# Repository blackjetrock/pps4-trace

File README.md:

# pps4-trace

Circuit to attempt to trace the address and data busses of the PPS-4 processor. the aim is to capture the ROM contents by sniffing the bus.
PPS-4 runs on -17V so circuit sits on 0V to -17v and divides down the inputs to 3V3.
PSU runs off PPS-4 supply

There's a few ROM image files I've managed to capture.

Although the bus tracing worked, it was difficult to work out exactly which ROM was bank switched and when. I therefore built a ROM dumper, desoldered a set of ROMs from a 920 and dumped them. This gave me the bank switching regime as the ROMs only responded to certain addressing. These ROMs were concatenated, effectively, and can be run in the simulator.
Details of the bank switching are in the simulator ROM file.

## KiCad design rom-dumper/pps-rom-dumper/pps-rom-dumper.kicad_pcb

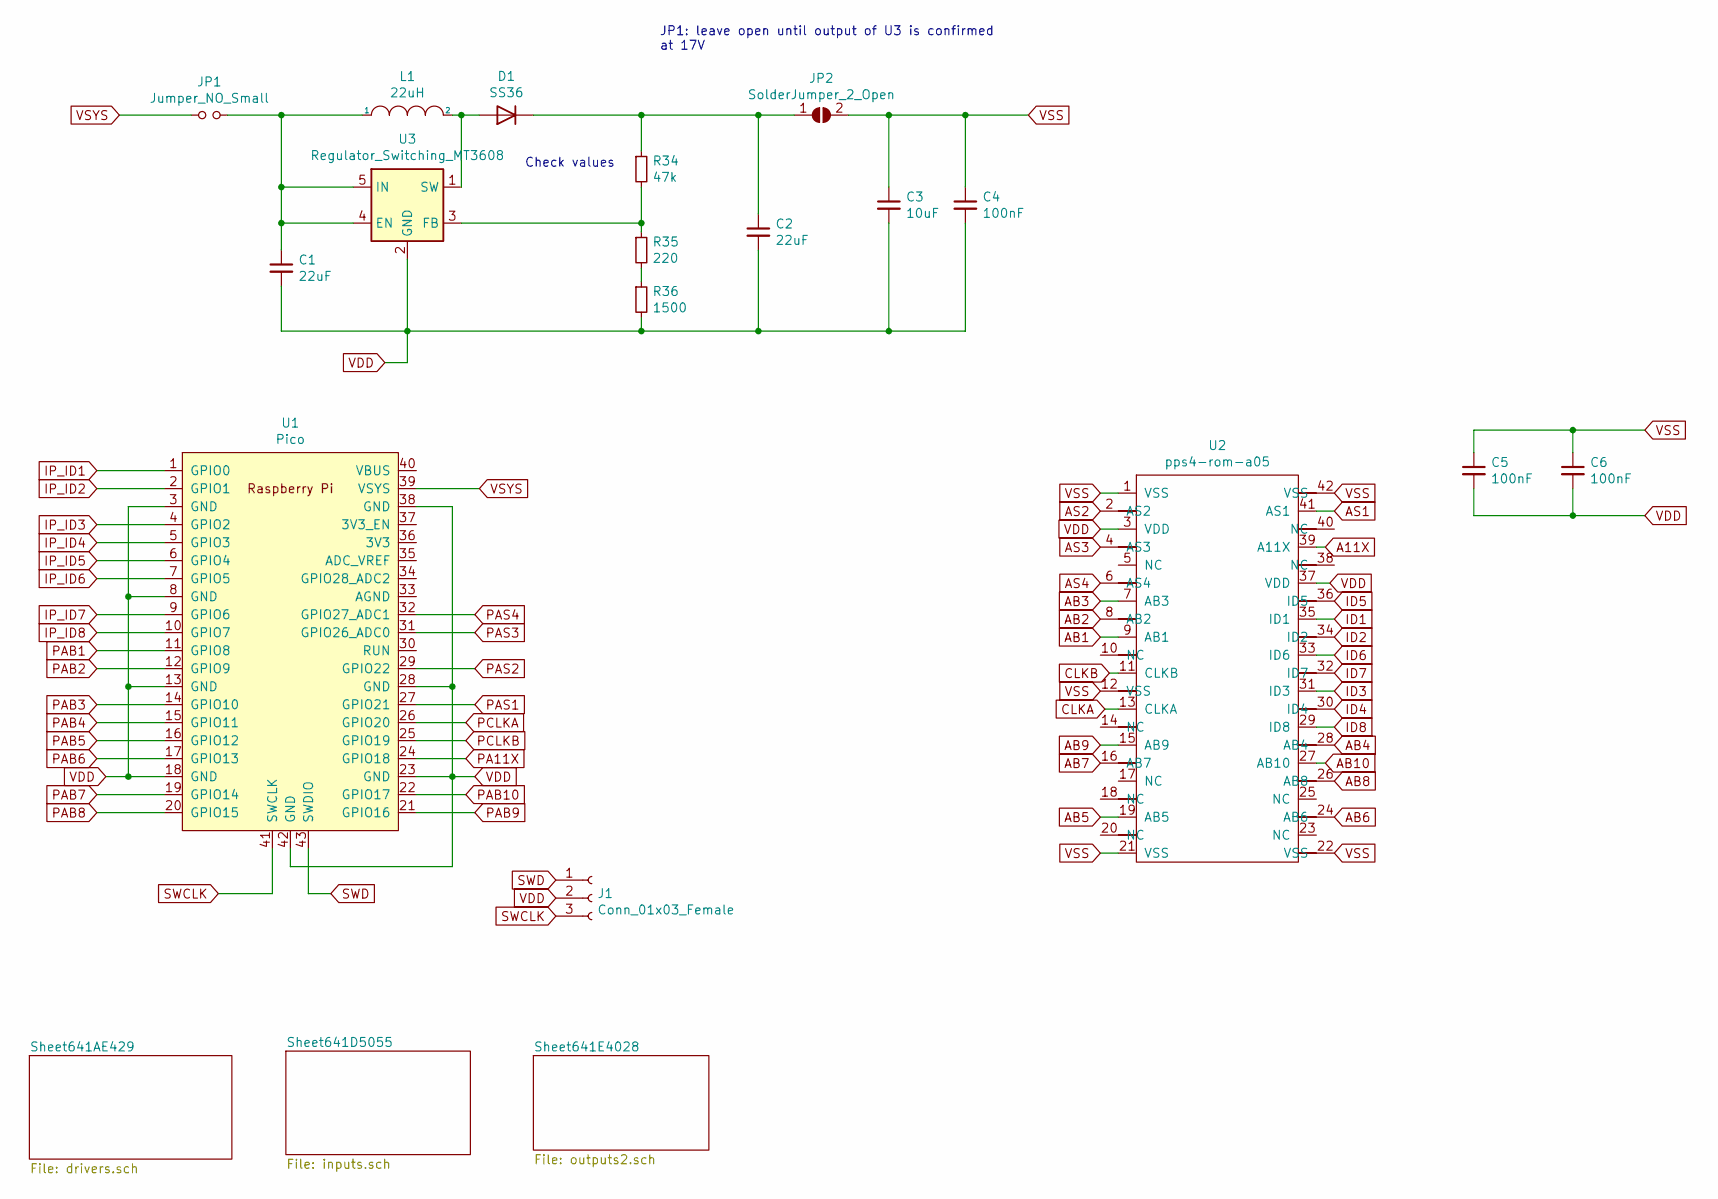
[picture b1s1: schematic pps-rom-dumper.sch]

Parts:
C1, C2: 22uF; C_1210_3225Metric_Pad1.33x2.70mm_HandSolder
C3: 10uF; C_1210_3225Metric_Pad1.33x2.70mm_HandSolder
C4, C5, C6: 100nF; C_1210_3225Metric_Pad1.33x2.70mm_HandSolder
D1: SS36; D_SOD-123
J1: Conn_01x03_Female; PinHeader_1x03_P2.54mm_Vertical
JP1: Jumper_NO_Small; SolderJumper-2_P1.3mm_Open_Pad0.8x0.8mm
JP2: SolderJumper_2_Open; SolderJumper-2_P1.3mm_Open_Pad0.8x0.8mm
L1: 22uH; L_Coilcraft_LPS5030
R34: 47k; R_0805_2012Metric
R35: 220; R_0805_2012Metric
R36: 1500; R_0805_2012Metric
U1: Pico; RPi_Pico_SMD_TH
U2: pps4-rom-a05; qip42
U3: Regulator_Switching_MT3608; SOT-23-6

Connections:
A11X: U2.39 (A11X); also elsewhere on the board
AB1: U2.9 (AB1); also elsewhere on the board
AB2: U2.8 (AB2); also elsewhere on the board
AB3: U2.7 (AB3); also elsewhere on the board
AB4: U2.28 (AB4); also elsewhere on the board
AB5: U2.19 (AB5); also elsewhere on the board
AB6: U2.24 (AB6); also elsewhere on the board
AB7: U2.16 (AB7); also elsewhere on the board
AB8: U2.26 (AB8); also elsewhere on the board
AB9: U2.15 (AB9); also elsewhere on the board
AB10: U2.27 (AB10); also elsewhere on the board
AS1: U2.41 (AS1); also elsewhere on the board
AS2: U2.2 (AS2); also elsewhere on the board
AS3: U2.4 (AS3); also elsewhere on the board
AS4: U2.6 (AS4); also elsewhere on the board
CLKA: U2.13 (CLKA); also elsewhere on the board
CLKB: U2.11 (CLKB); also elsewhere on the board
ID1: U2.35 (ID1); also elsewhere on the board
ID2: U2.34 (ID2); also elsewhere on the board
ID3: U2.31 (ID3); also elsewhere on the board
ID4: U2.30 (ID4); also elsewhere on the board
ID5: U2.36 (ID5); also elsewhere on the board
ID6: U2.33 (ID6); also elsewhere on the board
ID7: U2.32 (ID7); also elsewhere on the board
ID8: U2.29 (ID8); also elsewhere on the board
IP_ID1: U1.1 (GPIO0); also elsewhere on the board
IP_ID2: U1.2 (GPIO1); also elsewhere on the board
IP_ID3: U1.4 (GPIO2); also elsewhere on the board
IP_ID4: U1.5 (GPIO3); also elsewhere on the board
IP_ID5: U1.6 (GPIO4); also elsewhere on the board
IP_ID6: U1.7 (GPIO5); also elsewhere on the board
IP_ID7: U1.9 (GPIO6); also elsewhere on the board
IP_ID8: U1.10 (GPIO7); also elsewhere on the board
unnamed: C1.1, JP1.2, L1.1, U3.4 (EN), U3.5 (IN)
unnamed: C2.1, D1.1 (K), JP2.1 (A), R34.1
unnamed: D1.2 (A), L1.2, U3.1 (SW)
unnamed: R34.2, R35.1, U3.3 (FB)
unnamed: R35.2, R36.1
PA11X: U1.24 (GPIO18)
PAB1: U1.11 (GPIO8); also elsewhere on the board
PAB2: U1.12 (GPIO9); also elsewhere on the board
PAB3: U1.14 (GPIO10); also elsewhere on the board
PAB4: U1.15 (GPIO11); also elsewhere on the board
PAB5: U1.16 (GPIO12); also elsewhere on the board
PAB6: U1.17 (GPIO13); also elsewhere on the board
PAB7: U1.19 (GPIO14); also elsewhere on the board
PAB8: U1.20 (GPIO15); also elsewhere on the board
PAB9: U1.21 (GPIO16); also elsewhere on the board
PAB10: U1.22 (GPIO17); also elsewhere on the board
PAS1: U1.27 (GPIO21); also elsewhere on the board
PAS2: U1.29 (GPIO22); also elsewhere on the board
PAS3: U1.31 (GPIO26_ADC0); also elsewhere on the board
PAS4: U1.32 (GPIO27_ADC1); also elsewhere on the board
PCLKA: U1.26 (GPIO20); also elsewhere on the board
PCLKB: U1.25 (GPIO19); also elsewhere on the board
SWCLK: J1.3, U1.41 (SWCLK)
SWD: J1.1, U1.43 (SWDIO)
VDD: C1.2, C2.2, C3.2, C4.2, C5.2, C6.2, J1.2, R36.2, U1.3 (GND), U1.8 (GND), U1.13 (GND), U1.18 (GND), U1.23 (GND), U1.28 (GND), U1.38 (GND), U1.42 (GND), U2.3 (VDD), U2.37 (VDD), U3.2 (GND); also elsewhere on the board
VSS: C3.1, C4.1, C5.1, C6.1, JP2.2 (B), U2.1 (VSS), U2.12 (VSS), U2.21 (VSS), U2.22 (VSS), U2.42 (VSS); also elsewhere on the board
VSYS: JP1.1, U1.39 (VSYS)

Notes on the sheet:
Check values
JP1: leave open until output of U3 is confirmed at 17V

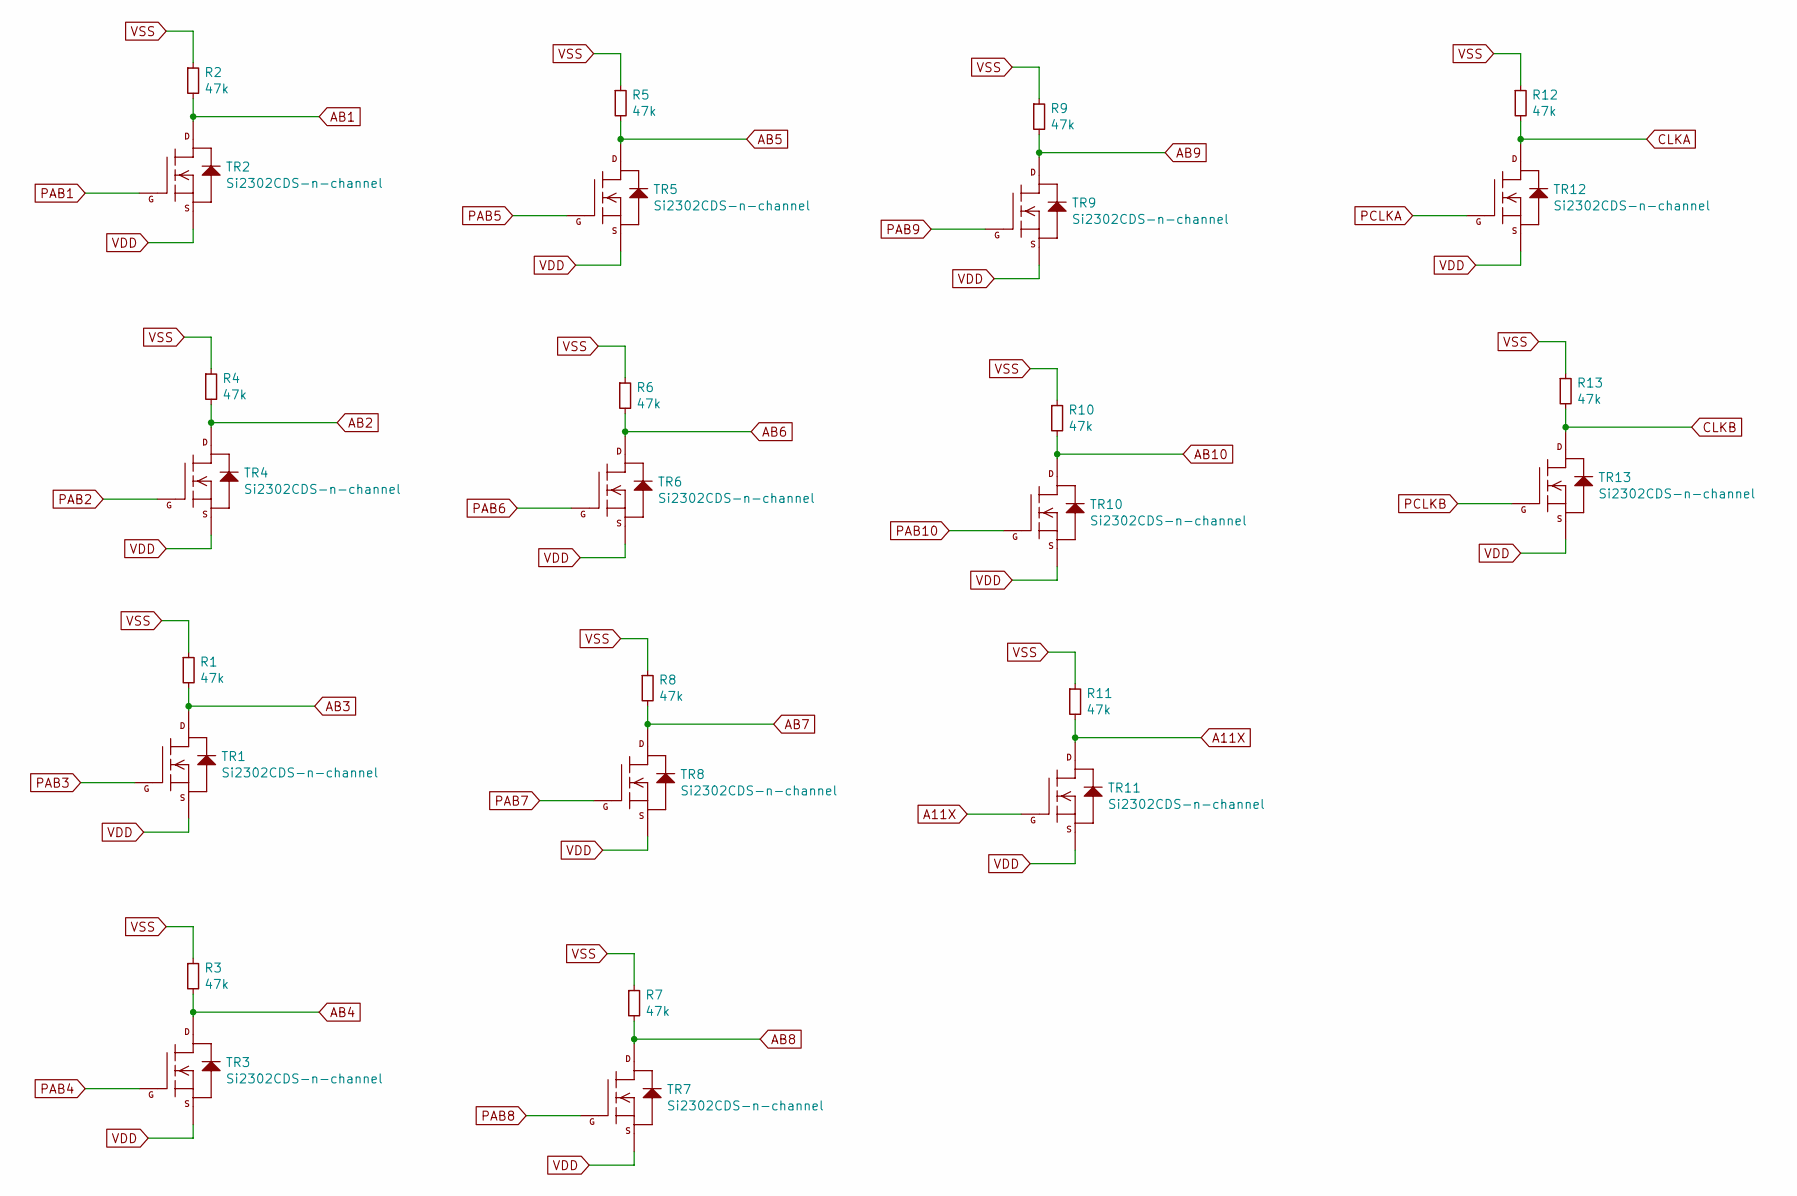
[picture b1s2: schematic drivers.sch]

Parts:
R1, R2, R3, R4, R5, R6, R7, R8, R9, R10, R11, R12, R13: 47k; R_0805_2012Metric_Pad1.20x1.40mm_HandSolder
TR1, TR2, TR3, TR4, TR5, TR6, TR7, TR8, TR9, TR10, TR11, TR12, TR13: Si2302CDS-n-channel; SOT-23

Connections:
A11X: R11.2, TR11.1 (G), TR11.3 (D); also elsewhere on the board
AB1: R2.2, TR2.3 (D); also elsewhere on the board
AB2: R4.2, TR4.3 (D); also elsewhere on the board
AB3: R1.2, TR1.3 (D); also elsewhere on the board
AB4: R3.2, TR3.3 (D); also elsewhere on the board
AB5: R5.2, TR5.3 (D); also elsewhere on the board
AB6: R6.2, TR6.3 (D); also elsewhere on the board
AB7: R8.2, TR8.3 (D); also elsewhere on the board
AB8: R7.2, TR7.3 (D); also elsewhere on the board
AB9: R9.2, TR9.3 (D); also elsewhere on the board
AB10: R10.2, TR10.3 (D); also elsewhere on the board
CLKA: R12.2, TR12.3 (D); also elsewhere on the board
CLKB: R13.2, TR13.3 (D); also elsewhere on the board
PAB1: TR2.1 (G); also elsewhere on the board
PAB2: TR4.1 (G); also elsewhere on the board
PAB3: TR1.1 (G); also elsewhere on the board
PAB4: TR3.1 (G); also elsewhere on the board
PAB5: TR5.1 (G); also elsewhere on the board
PAB6: TR6.1 (G); also elsewhere on the board
PAB7: TR8.1 (G); also elsewhere on the board
PAB8: TR7.1 (G); also elsewhere on the board
PAB9: TR9.1 (G); also elsewhere on the board
PAB10: TR10.1 (G); also elsewhere on the board
PCLKA: TR12.1 (G); also elsewhere on the board
PCLKB: TR13.1 (G); also elsewhere on the board
VDD: TR1.2 (S), TR2.2 (S), TR3.2 (S), TR4.2 (S), TR5.2 (S), TR6.2 (S), TR7.2 (S), TR8.2 (S), TR9.2 (S), TR10.2 (S), TR11.2 (S), TR12.2 (S), TR13.2 (S); also elsewhere on the board
VSS: R1.1, R2.1, R3.1, R4.1, R5.1, R6.1, R7.1, R8.1, R9.1, R10.1, R11.1, R12.1, R13.1; also elsewhere on the board

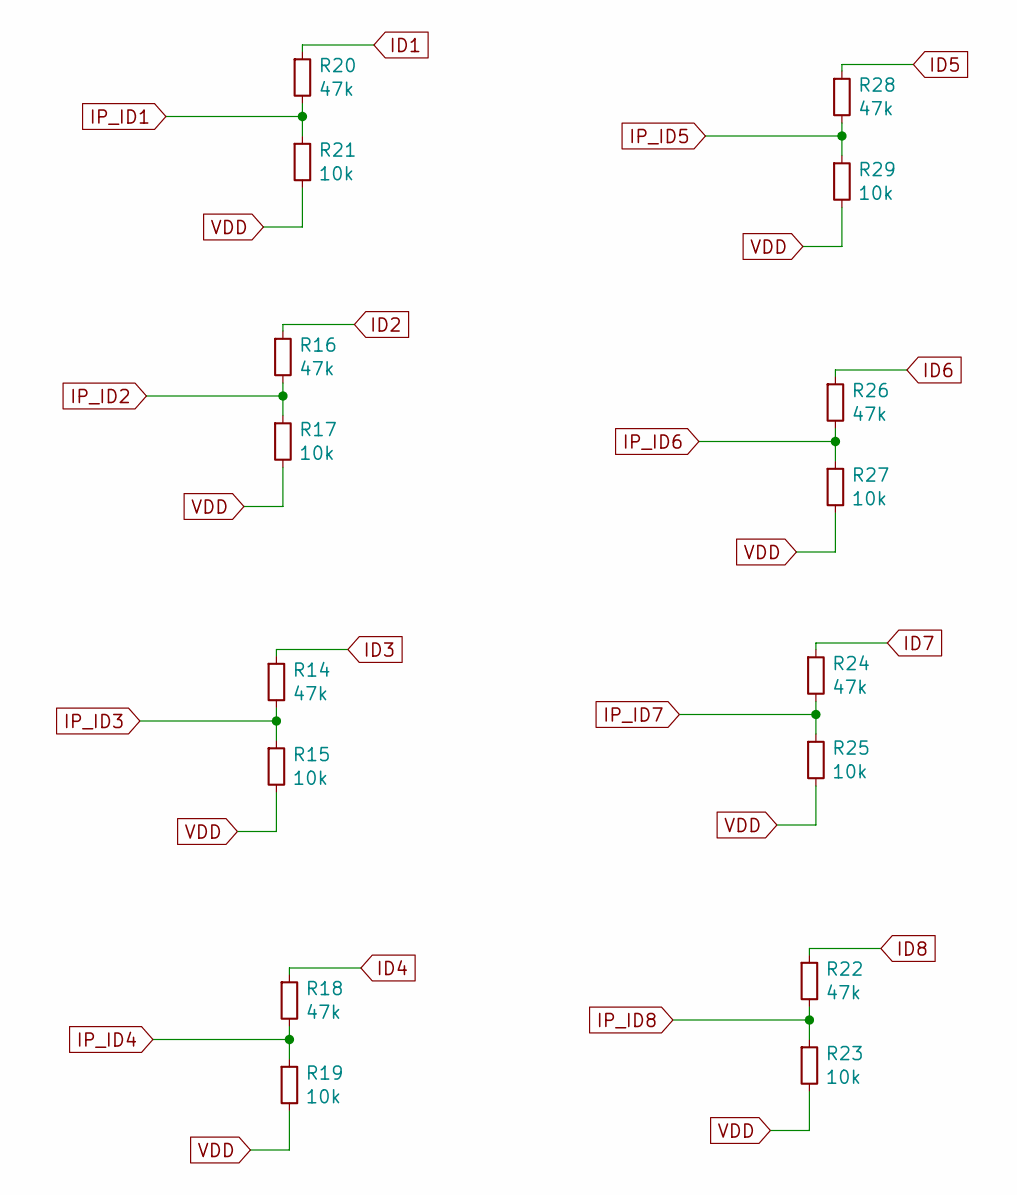
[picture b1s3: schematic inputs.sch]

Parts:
R14, R16, R18, R20, R22, R24, R26, R28: 47k; R_0805_2012Metric_Pad1.20x1.40mm_HandSolder
R15, R17, R19, R21, R23, R25, R27, R29: 10k; R_0805_2012Metric_Pad1.20x1.40mm_HandSolder

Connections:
ID1: R20.1; also elsewhere on the board
ID2: R16.1; also elsewhere on the board
ID3: R14.1; also elsewhere on the board
ID4: R18.1; also elsewhere on the board
ID5: R28.1; also elsewhere on the board
ID6: R26.1; also elsewhere on the board
ID7: R24.1; also elsewhere on the board
ID8: R22.1; also elsewhere on the board
IP_ID1: R20.2, R21.1; also elsewhere on the board
IP_ID2: R16.2, R17.1; also elsewhere on the board
IP_ID3: R14.2, R15.1; also elsewhere on the board
IP_ID4: R18.2, R19.1; also elsewhere on the board
IP_ID5: R28.2, R29.1; also elsewhere on the board
IP_ID6: R26.2, R27.1; also elsewhere on the board
IP_ID7: R24.2, R25.1; also elsewhere on the board
IP_ID8: R22.2, R23.1; also elsewhere on the board
VDD: R15.2, R17.2, R19.2, R21.2, R23.2, R25.2, R27.2, R29.2; also elsewhere on the board

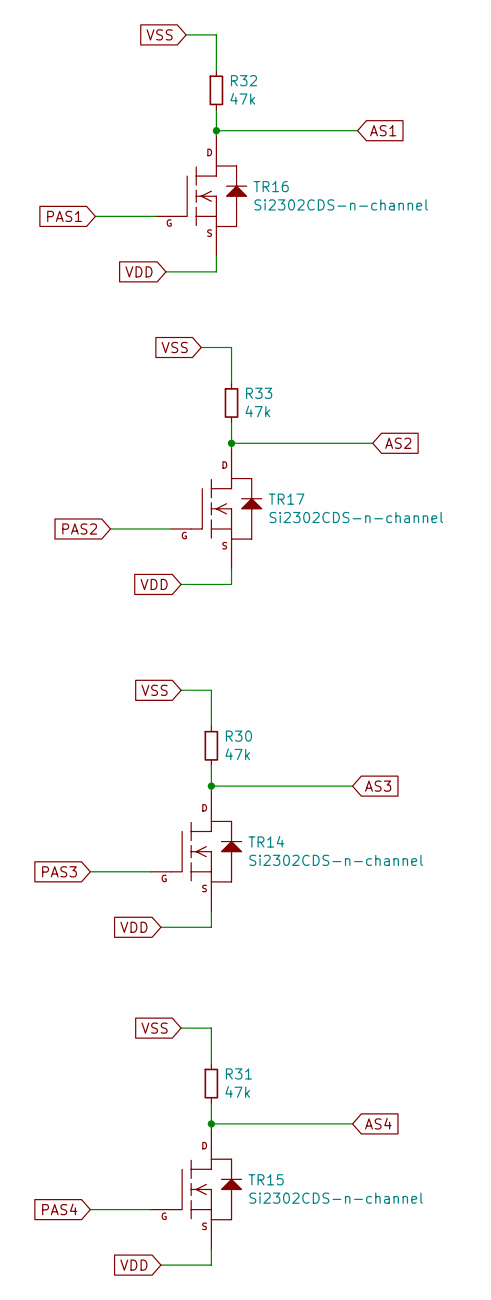
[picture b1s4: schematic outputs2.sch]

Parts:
R30, R31, R32, R33: 47k; R_0805_2012Metric_Pad1.20x1.40mm_HandSolder
TR14, TR15, TR16, TR17: Si2302CDS-n-channel; SOT-23

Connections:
AS1: R32.2, TR16.3 (D); also elsewhere on the board
AS2: R33.2, TR17.3 (D); also elsewhere on the board
AS3: R30.2, TR14.3 (D); also elsewhere on the board
AS4: R31.2, TR15.3 (D); also elsewhere on the board
PAS1: TR16.1 (G); also elsewhere on the board
PAS2: TR17.1 (G); also elsewhere on the board
PAS3: TR14.1 (G); also elsewhere on the board
PAS4: TR15.1 (G); also elsewhere on the board
VDD: TR14.2 (S), TR15.2 (S), TR16.2 (S), TR17.2 (S); also elsewhere on the board
VSS: R30.1, R31.1, R32.1, R33.1; also elsewhere on the board

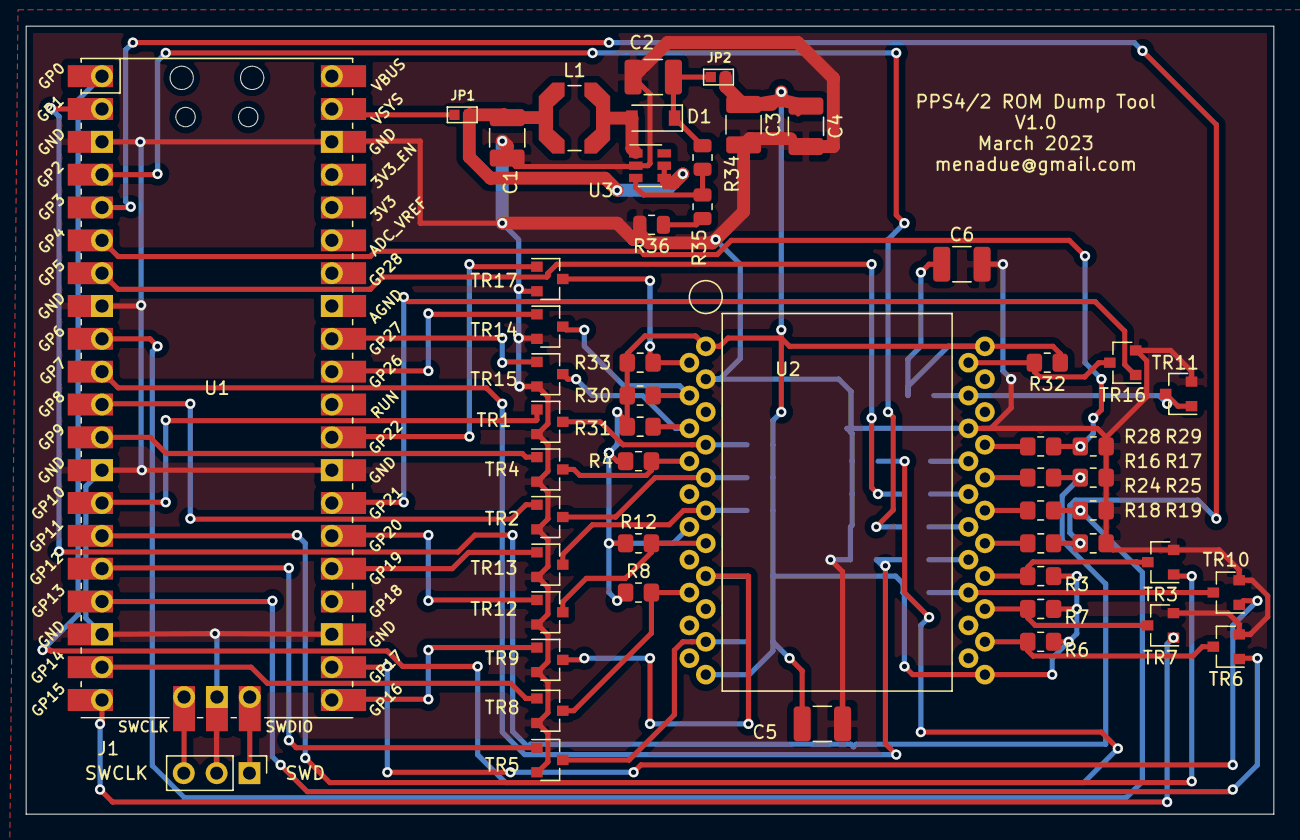
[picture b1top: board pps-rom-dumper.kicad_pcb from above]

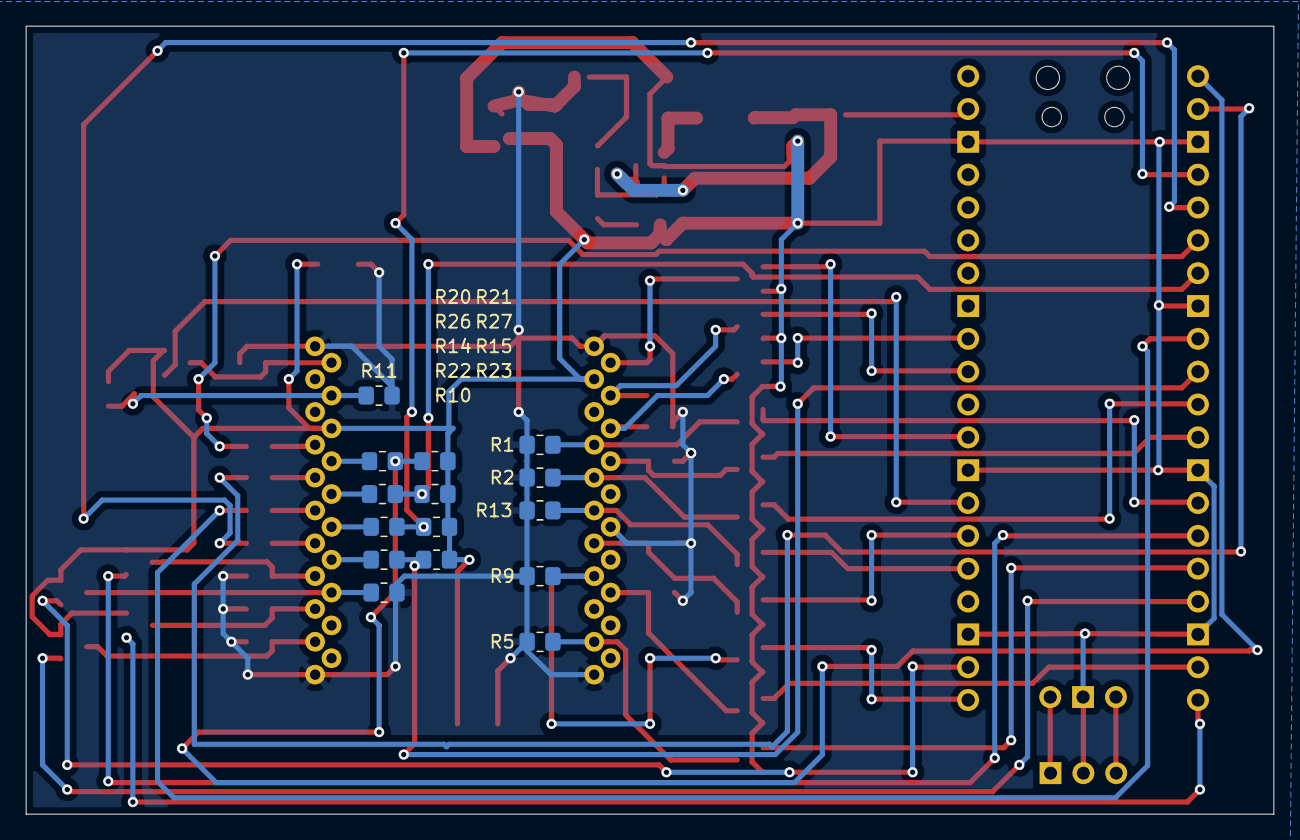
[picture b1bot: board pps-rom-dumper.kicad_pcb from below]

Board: 2 copper layers, 96.5 x 61.0 mm, 67 parts (15 on the bottom side), 59 nets.

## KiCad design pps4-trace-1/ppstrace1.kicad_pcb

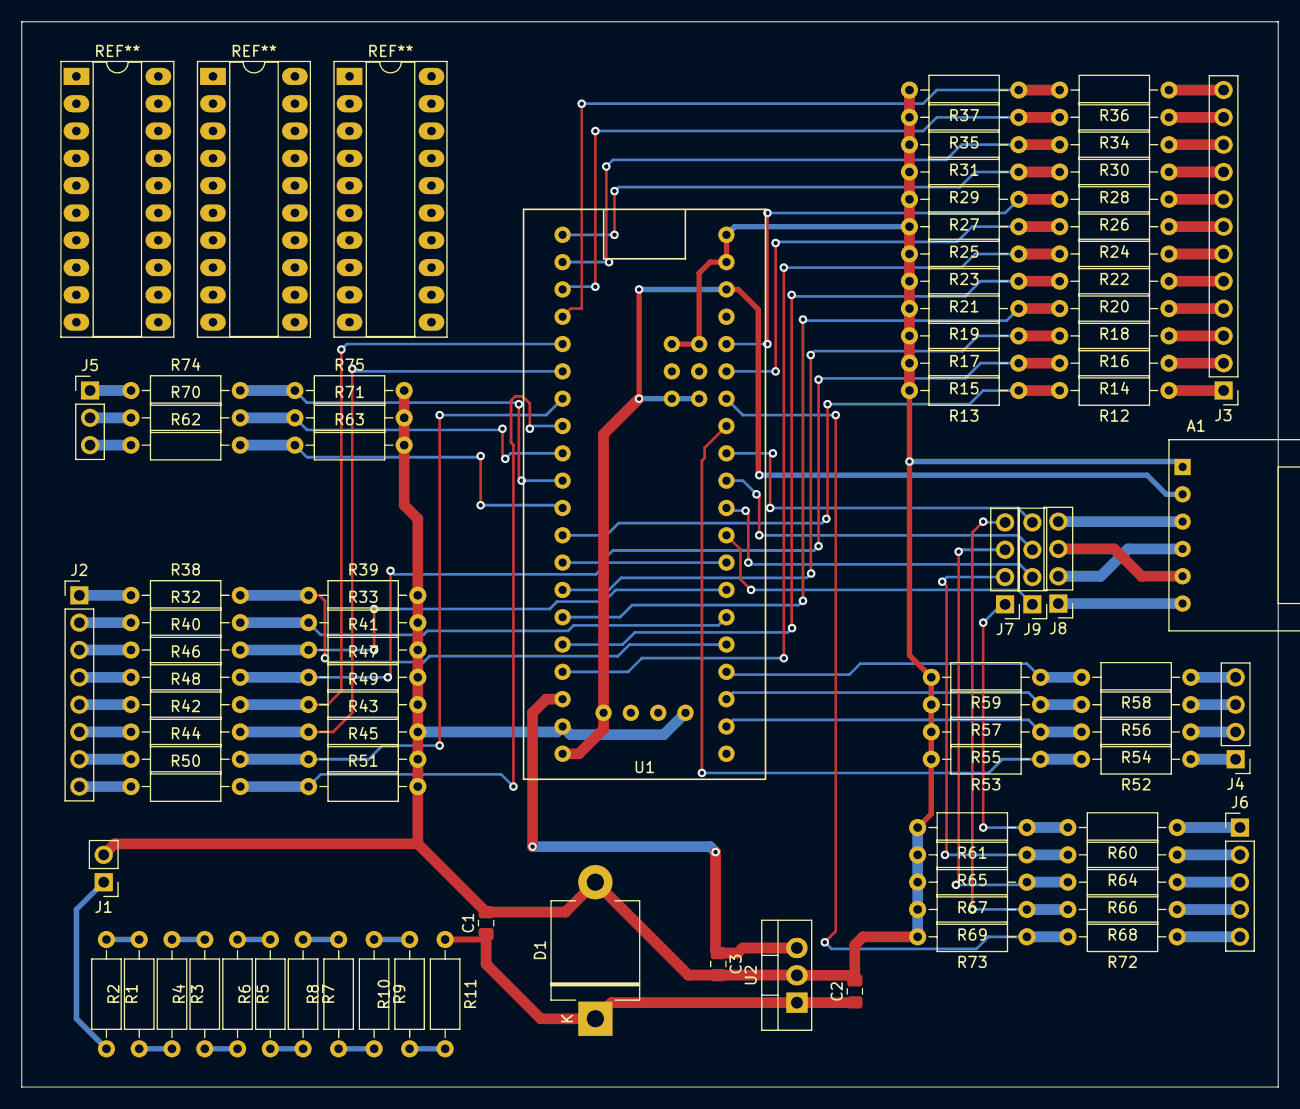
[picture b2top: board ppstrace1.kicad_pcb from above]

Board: 2 copper layers, 116.8 x 99.1 mm, 91 parts (0 on the bottom side), 87 nets.

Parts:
A1: SD_Card_Module_catalex; SD_Card_Module
C1, C2, C3: C_Small; C_0805_2012Metric_Pad1.15x1.40mm_HandSolder
D1: D_Zener; D_5KPW_P12.70mm_Horizontal
J1: Conn_01x02_Male; PinHeader_1x02_P2.54mm_Vertical
J2: Conn_01x08_Male; PinHeader_1x08_P2.54mm_Vertical
J3: Conn_01x12_Male; PinHeader_1x12_P2.54mm_Vertical
J4, J7, J8, J9: Conn_01x04_Male; PinHeader_1x04_P2.54mm_Vertical
J5: Conn_01x03_Male; PinHeader_1x03_P2.54mm_Vertical
J6: Conn_01x05_Male; PinHeader_1x05_P2.54mm_Vertical
R1, R2, R3, R4, R5, R6, R7, R8, R9, R10: 10R; R_Axial_DIN0207_L6.3mm_D2.5mm_P10.16mm_Horizontal
R11: R_Small; R_Axial_DIN0207_L6.3mm_D2.5mm_P10.16mm_Horizontal
R12, R14, R16, R18, R20, R22, R24, R26, R28, R30, R32, R34, R36, R38, R40, R42, R44, R46, R48, R50, R52, R54, R56, R58, R60, R62, R64, R66, R68, R70, R72, R74: 10k; R_Axial_DIN0207_L6.3mm_D2.5mm_P10.16mm_Horizontal
R13, R15, R17, R19, R21, R23, R25, R27, R29, R31, R33, R35, R37, R39, R41, R43, R45, R47, R49, R51, R53, R55, R57, R59, R61, R63, R65, R67, R69, R71, R73, R75: 2k2; R_Axial_DIN0207_L6.3mm_D2.5mm_P10.16mm_Horizontal
U1: BP; BLUEPILL
U2: LM7805_TO220; TO-220-3_Vertical

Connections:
+3V3: A1.2, U1.3V3
+5V: C3.1, U1.5V, U2.3
A1: J3.1, R12.1
A2: J3.2, R14.1
A3: J3.3, R16.1
A4: J3.4, R18.1
A5: J3.5, R20.1
A6: J3.6, R22.1
A7: J3.7, R24.1
A8: J3.8, R26.1
A9: J3.9, R28.1
A10: J3.10, R30.1
A11: J3.11, R34.1
A12: J3.12, R36.1
CLKA: J5.1, R74.1
CLKB: J5.2, R70.1
D1: J2.1, R38.1
D2: J2.2, R32.1
D3: J2.3, R40.1
D4: J2.4, R46.1
D5: J2.5, R48.1
D6: J2.6, R42.1
D7: J2.7, R44.1
D8: J2.8, R50.1
DO1: J4.1, R52.1
DO2: J4.2, R54.1
DO3: J4.3, R56.1
DO4: J4.4, R58.1
GND: A1.1, C1.2, C2.2, C3.2, D1.2, J1.2, R13.2, R15.2, R17.2, R19.2, R21.2, R23.2, R25.2, R27.2, R29.2, R31.2, R33.2, R35.2, R37.2, R39.2, R41.2, R43.2, R45.2, R47.2, R49.2, R51.2, R53.2, R55.2, R57.2, R59.2, R61.2, R63.2, R65.2, R67.2, R69.2, R71.2, R73.2, R75.2, U1.G, U2.2
IA1: R12.2, R13.1, U1.PB4
IA2: R14.2, R15.1, U1.PB5
IA3: R16.2, R17.1, U1.PB6
IA4: R18.2, R19.1, U1.PB7
IA5: R20.2, R21.1, U1.PB8
IA6: R22.2, R23.1, U1.PB9
IA7: R24.2, R25.1, U1.PB10
IA8: R26.2, R27.1, U1.PB11
IA9: R28.2, R29.1, U1.PB12
IA10: R30.2, R31.1, U1.PB13
IA11: R34.2, R35.1, U1.PB14
IA12: R36.2, R37.1, U1.PB15
ICLKA: R74.2, R75.1, U1.PA15
ICLKB: R70.2, R71.1, U1.PA12
ID1: R38.2, R39.1, U1.PA0
ID2: R32.2, R33.1, U1.PA1
ID3: R40.2, R41.1, U1.PA2
ID4: R46.2, R47.1, U1.PA3
ID5: R48.2, R49.1, U1.PA8
ID6: R42.2, R43.1, U1.PA9
ID7: R44.2, R45.1, U1.PA10
ID8: R50.2, R51.1, U1.PA11
IDO1: R52.2, R53.1, U1.PB0
IDO2: R54.2, R55.1, U1.PC13
IDO3: R56.2, R57.1, U1.PC14
IDO4: R58.2, R59.1, U1.PC15
IWIO: R62.2, R63.1, U1.PB3
IX1: J7.1, R60.2, R61.1
IX2: J7.2, R64.2, R65.1
IX3: J7.3, R66.2, R67.1
IX4: J7.4, R68.2, R69.1
IX5: R72.2, R73.1, U1.PB1
unnamed: A1.3, J8.4
unnamed: A1.4, J8.2
unnamed: A1.5, J8.3
unnamed: A1.6, J8.1
unnamed: C1.1, C2.1, D1.1, R11.1, U2.1
unnamed: J1.1, R1.2
unnamed: J9.1, U1.PA4
unnamed: J9.2, U1.PA5
unnamed: J9.3, U1.PA6
unnamed: J9.4, U1.PA7
unnamed: R1.1, R2.2
unnamed: R2.1, R3.2
unnamed: R3.1, R4.2
unnamed: R4.1, R5.2
unnamed: R5.1, R6.2
unnamed: R6.1, R7.2
unnamed: R7.1, R8.2
unnamed: R8.1, R9.2
unnamed: R10.1, R11.2
unnamed: R9.1, R10.2
WIO: J5.3, R62.1
X1: J6.1, R60.1
X2: J6.2, R64.1
X3: J6.3, R66.1
X4: J6.4, R68.1
X5: J6.5, R72.1

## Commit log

2020-10-26 Moved files about
2020-11-27 Added files
2020-12-05 Added sketch
2020-12-05 Added traces
2020-12-08 Added more traces, some broken. Trace processing script now decodes successfully after fixes to input processing.
2020-12-11 Added decoding scripts and files.
2020-12-11 Added traces taken from reset after a certain number of clock cycles.
2020-12-11 Added rom data file. It can be generated, but this is th ecurrent one with (I think) all code run on my broken 920/3 from reset to getting stuck in a loop.
2020-12-13 Added continuous capture and annotations.
2020-12-13 Added rom dumps There's 5K of ROM though, not 4K.
2020-12-13 Added dump to romdata file tool
2020-12-13 disassembly tool now uses filenames
2020-12-17 Updates. Added graphing code.
2020-12-17 Added anothr annotated file.
2020-12-17 Added simulator
2020-12-17 Updated simulator
2020-12-17 Simulator updates
2020-12-18 Null
2020-12-18 Null change
2020-12-18 Added files from old repo. Housekeeping
2020-12-18 Housekeeping
2020-12-18 Simulator fixes and updates Can now run a fair bit of code
2020-12-19 Updates to simulator and grapher
2020-12-19 Added example code
2020-12-19 Added example stuff
2020-12-19 More example stuff
2020-12-22 Updates to scripts
2020-12-22 Updatedannotation
2020-12-24 Updates to simulator
2020-12-24 More annotated listing. More data from capture runs
2021-01-12 Updated annoted listing
2021-03-12 Updated annotated ROM file
2021-03-12 Added file to run simulator
2021-03-12 Update to annotations
